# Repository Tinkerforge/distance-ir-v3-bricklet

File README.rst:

Distance IR Bricklet 3.0
========================

**This Bricklet is currently in development.**

This repository contains the firmware source code and the hardware design
files. The documentation generator configs can be found at
https://github.com/Tinkerforge/generators

Repository Content
------------------

software/:
 * examples/: Examples for all supported languages
 * build/: Compiled files
 * src/: Source code of firmware
 * Makefile: Makefile to build project

hardware/:
 * Contains KiCad project files and additionally schematics as PDF

datasheets/:
 * Contains datasheets for sensors and complex ICs that are used

Hardware
--------

The hardware is designed with the open source EDA Suite KiCad
(http://www.kicad.org). Before you are able to open the files,
you have to install the Tinkerforge kicad-libraries
(https://github.com/Tinkerforge/kicad-libraries). You can either clone
them directly in hardware/ or clone them in a separate folder and
symlink them into hardware/
(ln -s kicad_path/kicad-libraries project_path/hardware). After that you
can open the .pro file in hardware/ with KiCad and from there view and
modify the schematics and the PCB layout.

Software
--------

If you want to do your own Brick/Bricklet firmware development we highly
recommend that you use our build environment setup script and read the
tutorial (https://www.tinkerforge.com/en/doc/Tutorials/Tutorial_Build_Environment/Tutorial.html).

To compile the C code we recommend you to install the newest GNU Arm Embedded
Toolchain (https://launchpad.net/gcc-arm-embedded/+download).
You also need to install bricklib (https://github.com/Tinkerforge/bricklib)
and brickletlib (https://github.com/Tinkerforge/brickletlib).

You can either clone it directly in software/src/ or clone it in a
separate folder and symlink it into software/src/
(ln -s bricklib_path/bricklib project_path/software/src/ and
ln -s brickletlib_path/brickletlib project_path/software/src/).
Finally make sure to have CMake installed
(http://www.cmake.org/cmake/resources/software.html).

After that you can build the firmware by invoking make in software/.
The firmware (.bin) can then be found in software/build/ and uploaded
with brickv (click button "Flashing" on start screen).

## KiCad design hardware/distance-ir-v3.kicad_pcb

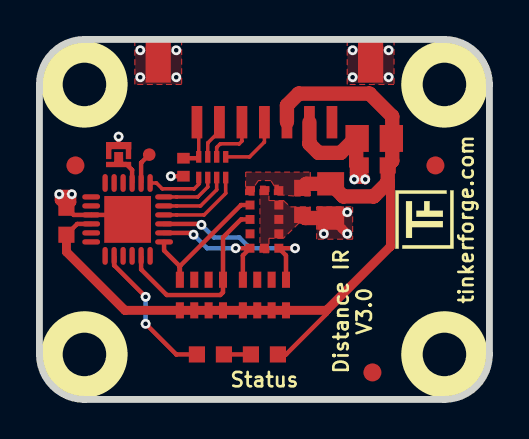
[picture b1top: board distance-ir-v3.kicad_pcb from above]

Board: 2 copper layers, 25.0 x 20.0 mm, 25 parts (2 on the bottom side), 18 nets.

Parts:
C1, C104: 100nF; C0603F
C2: 4,7uF; C0805E
C101: 10uF; C0805E
C102: 220pF; C0402F
C103: 1uF; C0603F
D101: blue; D0603F
Fiducial_Mark: VAL**; Fiducial_Mark
Fiducial_Mark#2, Fiducial_Mark#3: VAL**; Fiducial_Mark
P101: CON-SENSOR2
P102: DEBUG; DEBUG_PAD
P103: BOOT; SolderJumper
R101: 1k; R0603F
RP1: 10k; 0603X4
RP101: 82; 4X0402
RP102: 3k9; 0603X4
U1: VL53L1
U101: XMC1XXX; QFN24-4x4mm-0.5mm
U103, U104, U105, U106: DRILL; DRILL_NP
VAL: WEEE_7mm
VAL#2: CE_5mm

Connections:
GND: C1.2, C2.2, C101.1, C102.1, C103.1, C104.2, P101.2, P101.EP, P103.1, U1.2, U1.3, U1.4, U1.6, U1.12, U101.9, U101.EXP
GPIO: RP1.8, U1.7, U101.20
unnamed: C102.2, P101.7, RP101.4
unnamed: D101.2, R101.2
unnamed: P101.4, RP101.1
unnamed: P101.5, RP101.2
unnamed: P101.6, RP101.3
unnamed: P102.1, U101.2
unnamed: P103.2, U101.3
unnamed: R101.1, U101.14
S-CLK: RP101.7, U101.23
S-CS: RP101.8, U101.22
S-MISO: RP101.5, U101.1
S-MOSI: RP101.6, U101.24
SCL: RP102.8, U1.10, U101.19
SDA: RP102.5, U1.9, U101.17
VCC: C1.1, C2.1, C101.2, C103.2, C104.1, D101.1, P101.3, RP1.1, RP1.2, RP1.3, RP1.4, RP102.1, RP102.2, RP102.3, RP102.4, U1.1, U1.11, U101.10
XSHUT: RP1.5, U1.5, U101.21

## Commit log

2020-06-22 initial push
2020-06-22 pcb design
2020-06-22 added fiducial marks
2020-06-23 changed sda and scl
2020-07-10 changed footprint for incoming capacitors
2020-09-02 Add sym-lib-table
2021-10-25 Update KiCad link
    https://www.kicad.org/blog/2021/10/Avoid-links-to-former-kicad-domain/

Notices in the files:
hardware/distance-ir-v3.kicad_pcb:
Licensed under CERN OHL v.1.1
Copyright (©) 2020, T.Schneidermann
Copyright Tinkerforge GmbH 2020.
This documentation describes Open Hardware and is licensed under the
CERN OHL v. 1.1.
